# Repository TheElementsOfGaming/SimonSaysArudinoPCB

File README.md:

# Simon Says Game PCB

This repository hosts the KiCad and Gerber files needed to create a barebones Arduino-compatible board designed to play the Simon Says game. This project aims to provide enthusiasts and learners with an easy way to build and understand a classic game using modern electronics. The design is straightforward, making it an excellent project for those new to PCB design and electronics.

## Introduction

The Simon Says Game PCB is a fun and interactive way to get into electronics and programming. Using KiCad files, users can modify the design according to their needs, while the provided Gerber files are ready for manufacturing, allowing anyone to order a PCB directly from a fabricator.

## Getting Started

### Prerequisites

- KiCad 8.0 or later for editing the PCB design files.
- A PCB manufacturer to produce the board using the provided Gerber files. I use JLCPCB but feel free to use whatever is most comfortable for you.

### Installation

1. Clone this repository to your local machine
2. Open the KiCad project file to view, modify, or export the design.
3. Use the Gerber files to order PCBs from your preferred manufacturer (These currently aren't available since only the schematic has been created). 

## Hardware Requirements

To assemble and use the Simon Says Game PCB, you will need the following components:

- 1x Atmega328P Microcontroller (Any variant should work as long as it contains the Arduino bootloader)
- 4x LED (Red, Blue, Green, Yellow)
- 4x 220 Ohm resistors
- 1x Buzzer
- Miscellaneous: Solder, wire, power supply

## Usage

1. After assembling the PCB with the necessary components, upload the Simon Says game code to the microcontroller. You can find example Arduino sketches online or we can write your own. 
2. You'll also need to burn an Arduino bootloader onto the Atmega328P microcontroller. There are plenty of tutorials online to do this or you can purchase a microcontroller that already has the bootloader on it.

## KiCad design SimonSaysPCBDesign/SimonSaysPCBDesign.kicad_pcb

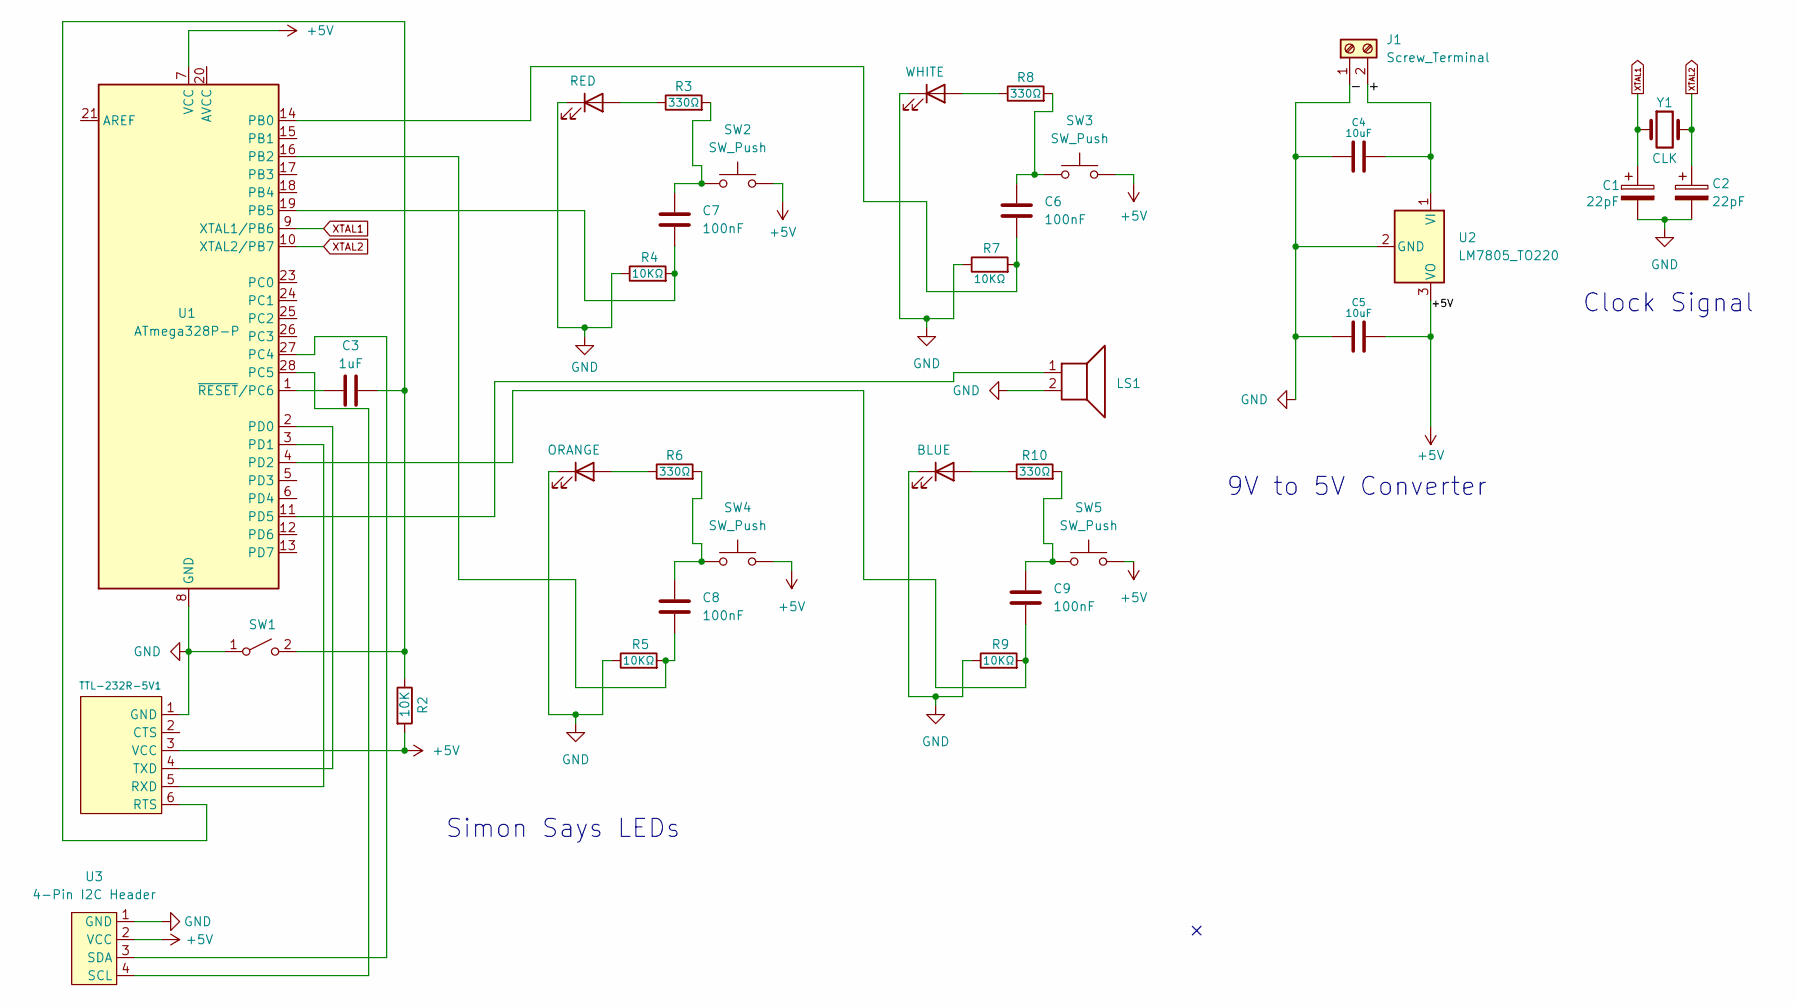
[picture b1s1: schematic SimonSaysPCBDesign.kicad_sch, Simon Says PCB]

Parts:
C1, C2: 22pF; C_0402_1005Metric
C3: 1uF; C_0402_1005Metric
C4, C5: 10uF; C_1206_3216Metric
C6, C7, C8, C9: 100nF; C_0402_1005Metric
D2: RED; LED_D5.0mm
D3: ORANGE; LED_D5.0mm
D4: WHITE; LED_D5.0mm
D5: BLUE; LED_D5.0mm
J1: Screw_Terminal; TerminalBlock_Phoenix_PT-1,5-2-5.0-H_1x02_P5.00mm_Horizontal
LS1: Speaker; PinHeader_1x02_P2.54mm_Vertical
R2: 10K; R_0402_1005Metric
R3, R6, R8, R10: 330Ω; R_0603_1608Metric
R4, R5, R7, R9: 10KΩ; R_0402_1005Metric
SW1: SW_SPST; SW_PUSH_6mm_H5mm
SW2, SW3, SW4, SW5: SW_Push; SW_PUSH_6mm_H5mm
TTL-232R-5V1: PinHeader_1x06_P2.54mm_Vertical
U1: ATmega328P-P; DIP-28_W7.62mm
U2: LM7805_TO220; TO-220-3_Horizontal_TabDown
U3: 4-Pin I2C Header; PinHeader_1x04_P2.54mm_Vertical
Y1: CLK; Crystal_SMD_2016-4Pin_2.0x1.6mm

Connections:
+5V: C5.2, R2.2, SW2.2, SW3.2, SW4.2, SW5.2, TTL-232R-5V1.3 (VCC), U1.7 (VCC), U2.3 (VO), U3.2 (VCC)
/+: C4.2, J1.2, U2.1 (VI)
GND: C1.2, C2.2, C4.1, C5.1, D2.1 (K), D3.1 (K), D4.1 (K), D5.1 (K), J1.1, LS1.2, R4.1, R5.1, R7.1, R9.1, SW1.1 (A), TTL-232R-5V1.1 (GND), U1.8 (GND), U1.22 (GND), U2.2 (GND), U3.1 (GND)
unnamed: C6.1, R8.2, SW3.1
unnamed: C7.1, R3.2, SW2.1
unnamed: C8.1, R6.2, SW4.1
unnamed: C9.1, R10.2, SW5.1
unnamed: D2.2 (A), R3.1
unnamed: D3.2 (A), R6.1
unnamed: D4.2 (A), R8.1
unnamed: D5.2 (A), R10.1
unnamed: C3.2, R2.1, SW1.2 (B), TTL-232R-5V1.6 (RTS)
unnamed: TTL-232R-5V1.5 (RXD), U1.3 (PD1)
unnamed: TTL-232R-5V1.4 (TXD), U1.2 (PD0)
unnamed: C6.2, R7.2, U1.14 (PB0)
unnamed: C8.2, R5.2, U1.16 (PB2)
unnamed: C7.2, R4.2, U1.19 (PB5)
unnamed: U1.27 (PC4), U3.3 (SDA)
unnamed: U1.28 (PC5), U3.4 (SCL)
unnamed: C9.2, R9.2, U1.4 (PD2)
unnamed: LS1.1, U1.11 (PD5)
unnamed: C3.1, U1.1 (~RESET/PC6)
XTAL1: C1.1, U1.9 (XTAL1/PB6), Y1.1
XTAL2: C2.1, U1.10 (XTAL2/PB7), Y1.2

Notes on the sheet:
Simon Says LEDs
Clock Signal
9V to 5V Converter

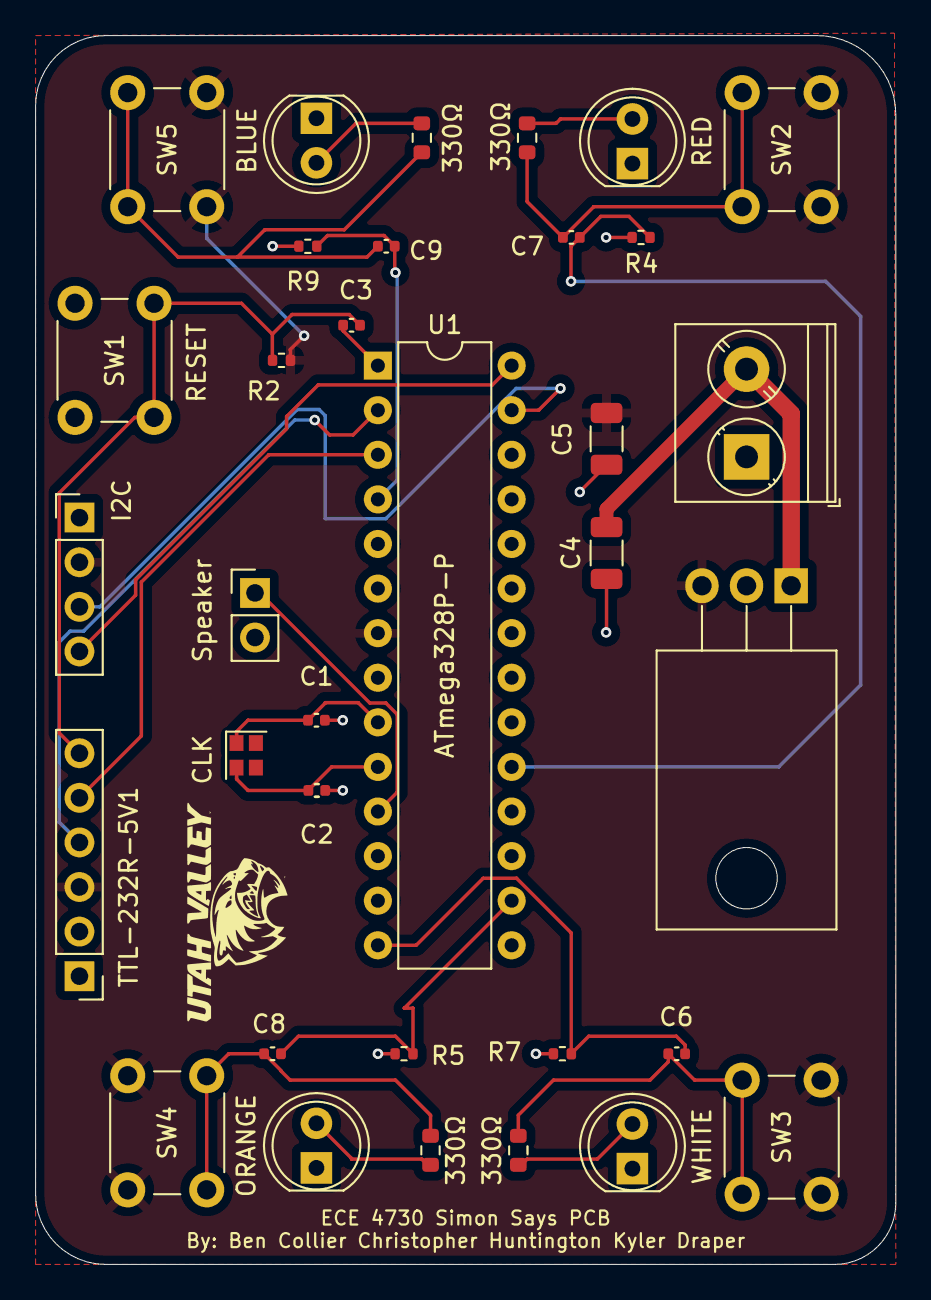
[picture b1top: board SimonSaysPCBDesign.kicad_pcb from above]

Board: 2 copper layers, 49.0 x 70.0 mm, 34 parts (0 on the bottom side), 24 nets.

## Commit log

2024-03-28 Began routing PCB
2024-04-01 Removed unnecessary file
2024-04-02 Almost finished routing PCB
2024-04-02 Ran a few more traces
2024-04-02 Created Gerber Files
2024-04-02 Added Gerber Files
